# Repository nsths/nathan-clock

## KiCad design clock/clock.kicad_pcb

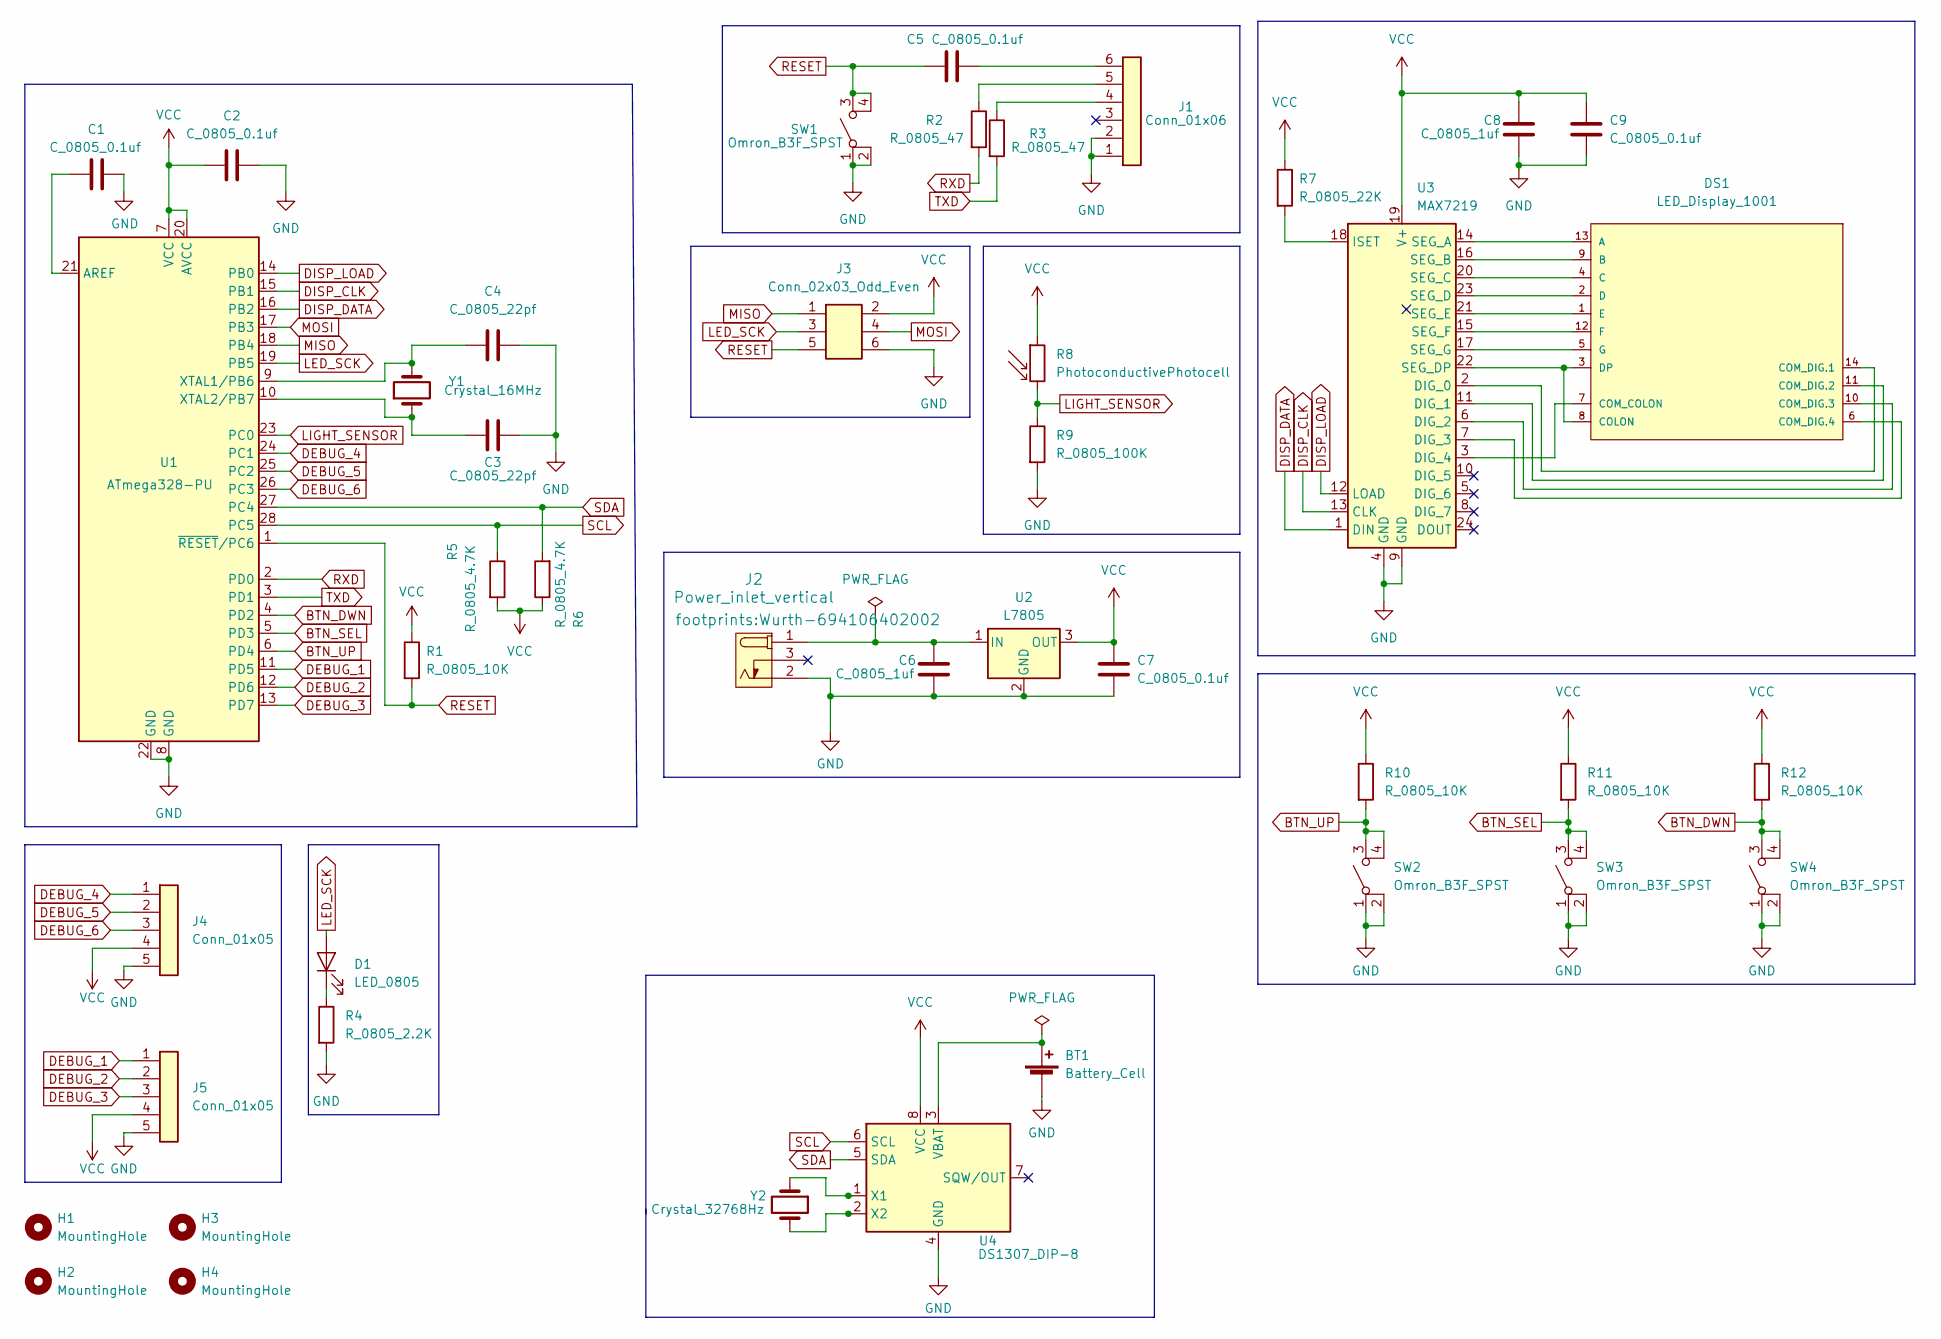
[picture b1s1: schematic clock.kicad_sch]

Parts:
BT1: Battery_Cell; BatteryHolder_Keystone_106_1x20mm; MPN BS-7; Digikey PN BS-7-ND
C1, C2, C5, C7, C9: C_0805_0.1uf; C_0805_2012Metric; Voltage N/A; Tolerance N/A; MPN 08055C104KAT2A; Digikey PN 478-1395-1-ND
C3, C4: C_0805_22pf; C_0805_2012Metric; Voltage N/A; Tolerance N/A; MPN CC0805JRNPO9BN220; Digikey PN 311-1103-1-ND
C6, C8: C_0805_1uf; C_0805_2012Metric; Voltage N/A; Tolerance N/A; MPN CC0805KKX7R8BB105; Digikey PN 311-1456-1-ND
D1: LED_0805; LED_0805_2012Metric; MPN 150080RS75000; Digikey PN 732-4984-1-ND
DS1: LED_Display_1001; Adafruit-1001-0-0-MFG; forward voltage 3.2V; reverse voltage 5V; mouser part number 485-1001; digikey description WHITE 7-SEGMENT CLOCK DISPLAY
H1, H2, H3, H4: MountingHole; MountingHole_3.2mm_M3
J1: Conn_01x06; PinHeader_1x06_P2.54mm_Vertical; MPN 61300611121; Digikey PN 732-5319-ND
J2: Power_inlet_vertical; Wurth-694106402002; MPN 694106402002; Digikey PN 732-5931-ND
J3: Conn_02x03_Odd_Even; PinHeader_2x03_P2.54mm_Vertical; MPN PRPC003DAAN-RC; Digikey PN S2011EC-03-ND
J4, J5: Conn_01x05; PinHeader_1x05_P2.54mm_Vertical; MPN 61300511121; Digikey PN 732-5318-ND
R1, R10, R11, R12: R_0805_10K; R_0805_2012Metric; Tolerance N/A; MPN RC0805FR-0710KL; Digikey PN 311-10.0KCRCT-ND
R2, R3: R_0805_47; R_0805_2012Metric; Tolerance N/A; Mouser PN N/A; Digikey PN RC0805FR-0747RL
R4: R_0805_2.2K; R_0805_2012Metric; Tolerance N/A; MPN N/A; Digikey PN 311-2.20KCRCT-ND
R5, R6: R_0805_4.7K; R_0805_2012Metric; Tolerance N/A; MPN RC0805FR-074K7L; Digikey PN 311-4.70KCRCT-ND
R7: R_0805_22K; R_0805_2012Metric; Tolerance N/A; MPN RC0805FR-0722KL; Digikey PN 311-22.0KCRCT-ND
R8: PhotoconductivePhotocell; R_LDR_4.9x4.2mm_P2.54mm_Vertical; Voltage N/A; Tolerance N/A; MPN PDV-P8103; Digikey PN PDV-P8103-ND
R9: R_0805_100K; R_0805_2012Metric; Tolerance N/A; MPN RC0805FR-07100KL; Digikey PN 311-100KCRCT-ND
SW1, SW2, SW3, SW4: Omron_B3F_SPST; SW_SPST_Omron_B3FS-100xP; MPN B3FS-1000P; Digikey PN SW423CT-ND
U1: ATmega328-PU; DIP-28_W7.62mm; MPN ED281DT; Digikey PN ED3050-5-ND
U2: L7805; TO-252-2
U3: MAX7219; DIP-24_W7.62mm; MPN ED241DT; Digikey PN ED3049-5-ND
U4: DS1307_DIP-8; DIP-8_W7.62mm; MPN A 08-LC-TT; Digikey PN AE9986-ND
Y1: Crystal_16MHz; Crystal_SMD_HC49-SD; MPN ECS-160-20-5PXDN-TR; Digikey PN XC1299CT-ND
Y2: Crystal_32768Hz; Crystal_SMD_2Pin_3.2x1.5mm; MPN Q 0,032768-JTX310-12,5-20-T1-HMR-50K-LF; Digikey PN 1908-1314-1-ND

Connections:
BTN_DWN: R12.2, SW4.3 (B), SW4.4 (B), U1.4 (PD2)
BTN_SEL: R11.2, SW3.3 (B), SW3.4 (B), U1.5 (PD3)
BTN_UP: R10.2, SW2.3 (B), SW2.4 (B), U1.6 (PD4)
DEBUG_1: J5.1, U1.11 (PD5)
DEBUG_2: J5.2, U1.12 (PD6)
DEBUG_3: J5.3, U1.13 (PD7)
DEBUG_4: J4.1, U1.24 (PC1)
DEBUG_5: J4.2, U1.25 (PC2)
DEBUG_6: J4.3, U1.26 (PC3)
DISP_CLK: U1.15 (PB1), U3.13 (CLK)
DISP_DATA: U1.16 (PB2), U3.1 (DIN)
DISP_LOAD: U1.14 (PB0), U3.12 (LOAD)
GND: BT1.2 (-), C1.2, C2.2, C3.2, C4.2, C6.2, C7.2, C8.2, C9.2, J1.1, J1.2, J2.2 (OUT), J3.6, J4.5, J5.5, R4.2, R9.2, SW1.1 (A), SW1.2 (A), SW2.1 (A), SW2.2 (A), SW3.1 (A), SW3.2 (A), SW4.1 (A), SW4.2 (A), U1.8 (GND), U1.22 (GND), U2.2 (GND), U3.4 (GND), U3.9 (GND), U4.4 (GND)
LED_SCK: D1.2 (A), J3.3, U1.19 (PB5)
LIGHT_SENSOR: R8.2, R9.1, U1.23 (PC0)
MISO: J3.1, U1.18 (PB4)
MOSI: J3.4, U1.17 (PB3)
unnamed: BT1.1 (+), U4.3 (VBAT)
unnamed: C1.1, U1.21 (AREF)
unnamed: C3.1, U1.10 (XTAL2/PB7), Y1.1
unnamed: C4.1, U1.9 (XTAL1/PB6), Y1.2
unnamed: C5.2, J1.6
unnamed: C6.1, J2.1 (POLE), U2.1 (IN)
unnamed: D1.1 (K), R4.1
unnamed: DS1.1 (E), U3.21 (SEG_E)
unnamed: DS1.2 (D), U3.23 (SEG_D)
unnamed: DS1.3 (DP), DS1.8 (COLON), U3.22 (SEG_DP)
unnamed: DS1.4 (C), U3.20 (SEG_C)
unnamed: DS1.5 (G), U3.17 (SEG_G)
unnamed: DS1.6 (COM_DIG.4), U3.7 (DIG_3)
unnamed: DS1.7 (COM_COLON), U3.3 (DIG_4)
unnamed: DS1.9 (B), U3.16 (SEG_B)
unnamed: DS1.10 (COM_DIG.3), U3.6 (DIG_2)
unnamed: DS1.11 (COM_DIG.2), U3.11 (DIG_1)
unnamed: DS1.12 (F), U3.15 (SEG_F)
unnamed: DS1.13 (A), U3.14 (SEG_A)
unnamed: DS1.14 (COM_DIG.1), U3.2 (DIG_0)
unnamed: J1.4, R3.1
unnamed: J1.5, R2.1
unnamed: R7.2, U3.18 (ISET)
unnamed: U4.1 (X1), Y2.1
unnamed: U4.2 (X2), Y2.2
RESET: C5.1, J3.5, R1.2, SW1.3 (B), SW1.4 (B), U1.1 (~RESET/PC6)
RXD: R2.2, U1.2 (PD0)
SCL: R5.1, U1.28 (PC5), U4.6 (SCL)
SDA: R6.2, U1.27 (PC4), U4.5 (SDA)
TXD: R3.2, U1.3 (PD1)
VCC: C2.1, C7.1, C8.1, C9.1, J3.2, J4.4, J5.4, R1.1, R5.2, R6.1, R7.1, R8.1, R10.1, R11.1, R12.1, U1.7 (VCC), U1.20 (AVCC), U2.3 (OUT), U3.19 (V+), U4.8 (VCC)

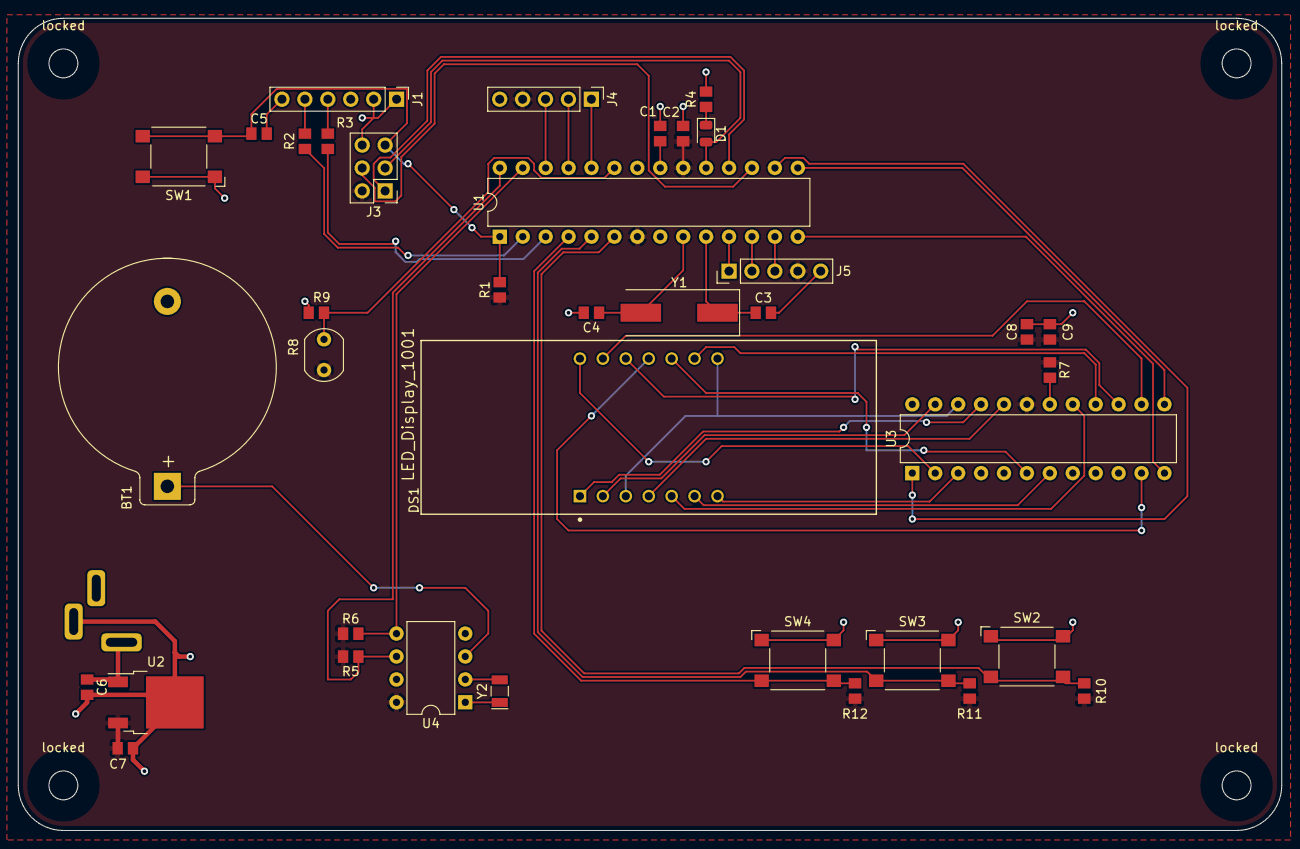
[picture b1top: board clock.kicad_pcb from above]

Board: 2 copper layers, 140.0 x 90.0 mm, 43 parts (1 on the bottom side), 48 nets.

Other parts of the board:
locked: MountingHole; MountingHole_3.2mm_M3
locked#2, locked#3, locked#4: MountingHole; MountingHole_3.2mm_M3

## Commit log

2022-06-12 adding KiCad template files
    template from HPS
2022-06-23 kinda week 2 deliverables
2022-07-12 appending the clock
2022-07-13 pre review schematic
2022-07-14 lil changes
2022-07-14 ewwww
2022-07-19 did a copper pour
2022-07-19 adjusted a lil schemaric
2022-07-20 lots o' changes
2022-07-20 new traces
2022-07-20 pretty close to done
2022-07-20 70% there
2022-07-21 pre check finish
2022-07-21 DRC Checked!
2022-07-21 gerbering n stuff
2022-07-21 more and more changes
2022-07-21 appended bom
